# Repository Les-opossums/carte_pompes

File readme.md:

# Carte pompes - opossum 2025

Ce repository à pour objectif la création de cartes éléctroniques pour des pompes 5V pour le système de ventouses du robot de la Coupe de France de robotique 2025.
Les cartes ont été designé avec kicad 8.0.

## Les pompes
Le pompes utilisées sont de ce type :

## Le schéma électrique
Chaque carte sert au contrôle :
- d'une pompe
- d'une éléctrovanne

## L'intégration mécanique
### 1 - Le pcb :
Le pcb est soudable directement sur la pompe:
<div style="display: flex; justify-content: space-around;">

</div>

### 2 - système de pompes :

Voici un exemple d'intégration dans le robot 2025 :

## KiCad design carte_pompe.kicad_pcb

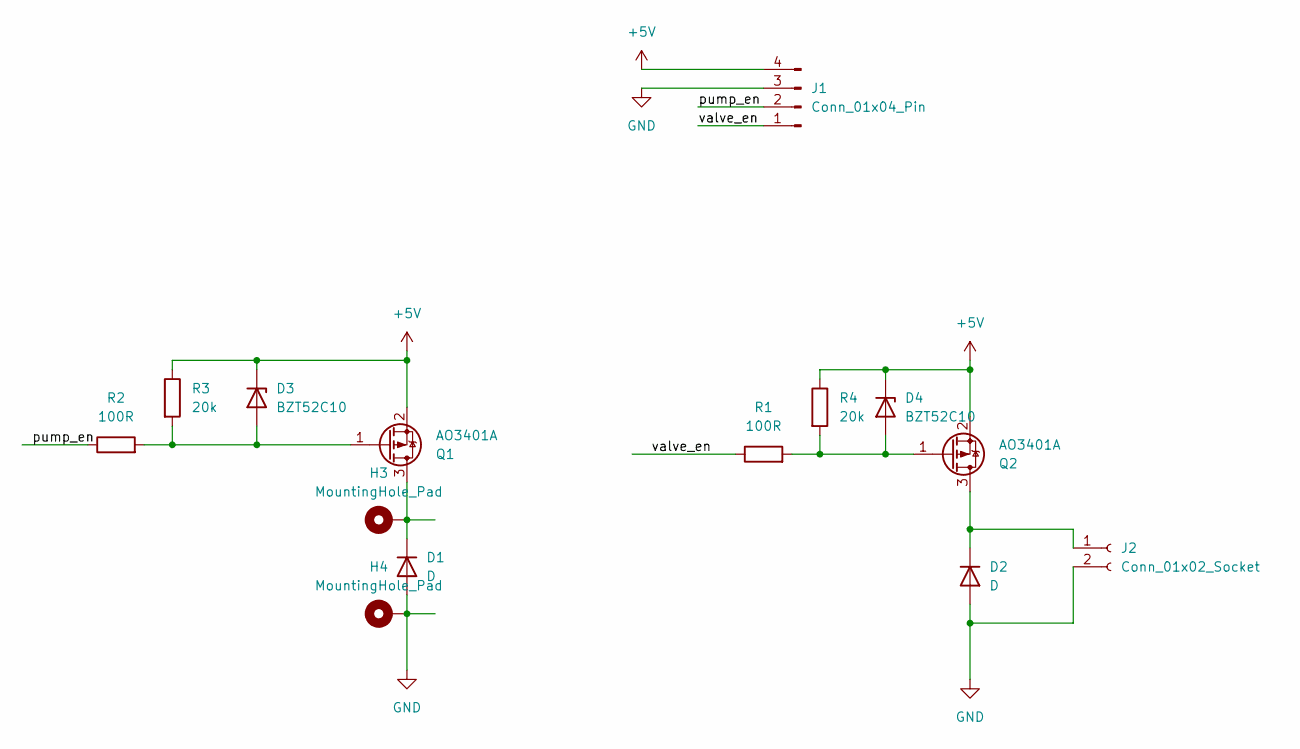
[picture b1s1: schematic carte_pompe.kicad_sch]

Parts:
D1, D2: D; D_SOD-123
D3, D4: BZT52C10; D_SOD-123
H3, H4: MountingHole_Pad; MountingHole_2.2mm_M2_DIN965_Pad
J1: Conn_01x04_Pin; JST_XH_B4B-XH-A_1x04_P2.50mm_Vertical
J2: Conn_01x02_Socket; PinHeader_1x02_P2.54mm_Vertical
Q1, Q2: AO3401A; SOT-23
R1, R2: 100R; R_0603_1608Metric_Pad0.98x0.95mm_HandSolder
R3, R4: 20k; R_0603_1608Metric_Pad0.98x0.95mm_HandSolder

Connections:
+5V: D3.1 (K), D4.1 (K), J1.4, Q1.2 (S), Q2.2 (S), R3.1, R4.1
/pump_en: J1.2, R2.1
/valve_en: J1.1, R1.1
GND: D1.2 (A), D2.2 (A), H4.1, J1.3, J2.2
unnamed: D1.1 (K), H3.1, Q1.3 (D)
unnamed: D2.1 (K), J2.1, Q2.3 (D)
unnamed: D3.2 (A), Q1.1 (G), R2.2, R3.2
unnamed: D4.2 (A), Q2.1 (G), R1.2, R4.2

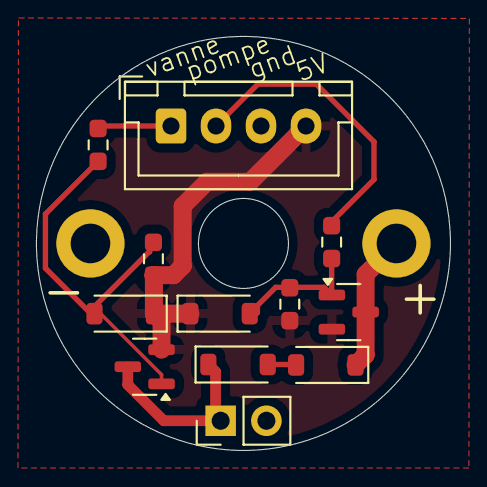
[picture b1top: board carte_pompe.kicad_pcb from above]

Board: 2 copper layers, 23.0 x 23.0 mm, 14 parts (0 on the bottom side), 8 nets.

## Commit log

2024-12-22 add text
2024-12-23 add readme
